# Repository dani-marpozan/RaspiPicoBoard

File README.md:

# Raspberry Pi Pico dev board 

This project is based on RP2040 microcontroller

Model 3D

## Schematic

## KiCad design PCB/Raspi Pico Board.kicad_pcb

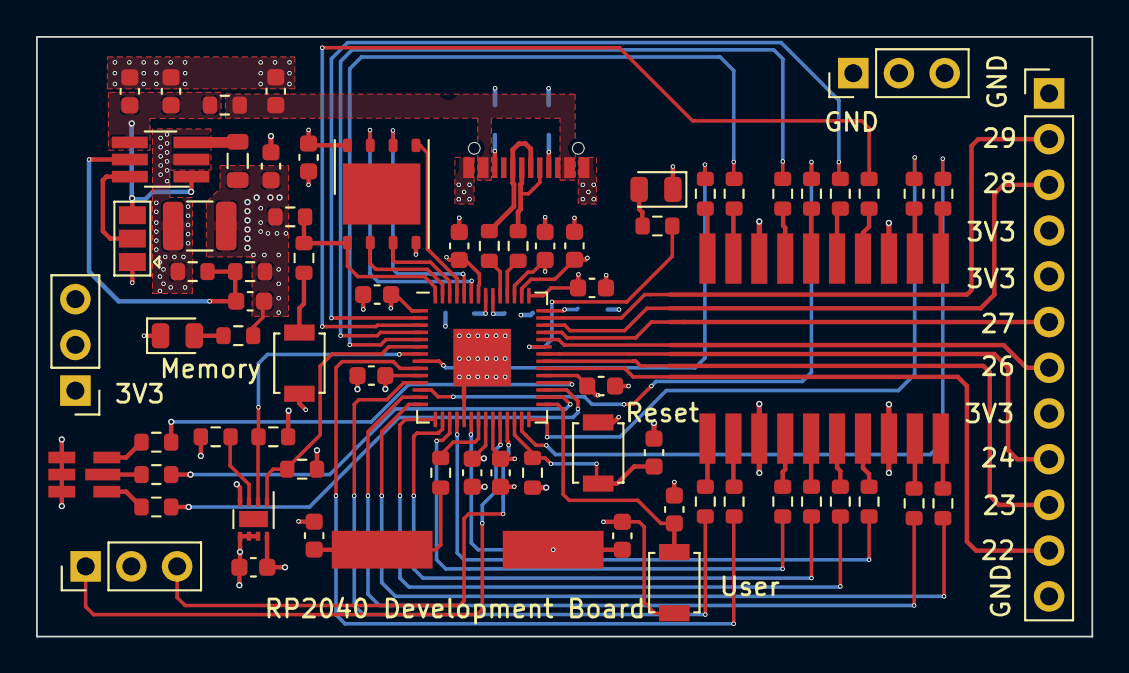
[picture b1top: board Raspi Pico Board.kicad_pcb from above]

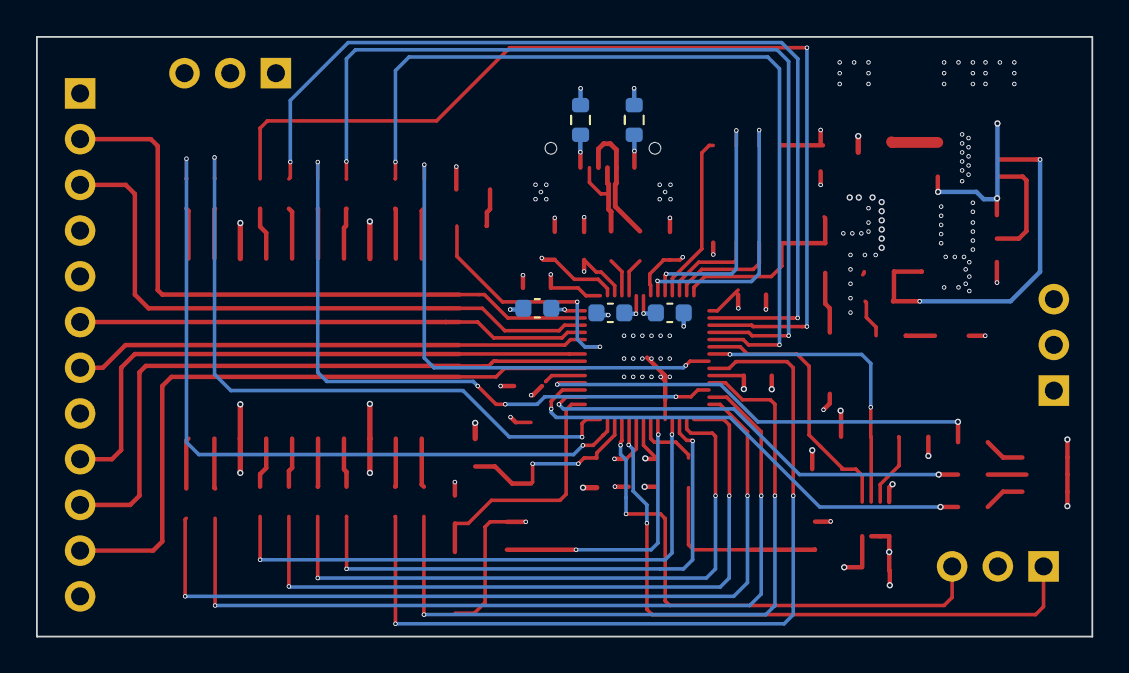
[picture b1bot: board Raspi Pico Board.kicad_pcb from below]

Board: 4 copper layers, 58.6 x 33.3 mm, 78 parts (5 on the bottom side), 79 nets.

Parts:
C1, C2, C7, C8, C9, C10, C11, C12, C15, C16, C17, C18, C19, C22, C23: 100n; C_0603_1608Metric
C3, C4: 2u2; C_0603_1608Metric
C5, C13, C14: 1u; C_0603_1608Metric
C6: 33u; C_1210_3225Metric
C20, C21: 27p; C_0603_1608Metric
C24: 10n; C_0603_1608Metric
D1, D2: LED; LED_0805_2012Metric
D4: ARGB1313HS-TR; RGB_ARGB1313HS-TR
FB1: 120R; R_0603_1608Metric
J1: USB4105; USBC_4105
J2, J4, J5: Conn_01x03_Pin; PinHeader_1x03_P2.54mm_Vertical
J3: Conn_01x12_Pin; PinHeader_1x12_P2.54mm_Vertical
JP1: SolderJumper_3_Open; SolderJumper-3_P1.3mm_Open_Pad1.0x1.5mm
L1: 10u; L_0805_2012Metric
R1, R2: 5k1; R_0603_1608Metric
R3: 887k; R_0603_1608Metric
R4: 280k; R_0603_1608Metric
R5: 150; R_0603_1608Metric
R6: 10k; R_0603_1608Metric
R7, R8, R11, R12, R13, R14, R15: 1k; R_0603_1608Metric
R9, R10: 27.4; R_0603_1608Metric
R16, R17, R18, R19, R20, R21, R22, R23, R24, R25, R26, R27, R28, R29, R30, R31, R32, R33, R34: 5k; R_0603_1608Metric
SW1, SW2, SW3: SW_Push; SW_SPST_B3U-1000P
U1: RP2040; QFN-56-1EP_7x7mm_P0.4mm_EP3.2x3.2mm
U2: W25Q128JV; WSON-8-1EP_6x5mm_P1.27mm_EP3.4x4.3mm
U3: LTC3405; TSOT-23-6_HandSoldering
U4: ACDC02-41SGWA-F01; 7DIG_ACDC02-41SGWA-F01
U5: TMP1075DSGT; WSON-8-1EP_2x2mm_P0.5mm_EP0.9x1.6mm
Y1: ABLS-12.000MHZ-B4-T

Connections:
+1V1: C14.1, C15.1, C16.1, U1.23 (DVDD), U1.45 (VREG_VOUT), U1.50 (DVDD)
+3V3: C4.1, C5.1, C6.1, C7.1, C8.1, C9.1, C10.1, C11.1, C12.1, C13.1, C17.1, C18.1, C19.1, C24.1, J3.4, J3.5, J3.8, J5.1, J5.2, J5.3, L1.2, R3.1, R5.1, R6.1, R11.2, R16.2, R17.2, R18.2, U1.1 (IOVDD), U1.10 (IOVDD), U1.22 (IOVDD), U1.33 (IOVDD), U1.42 (IOVDD), U1.43 (ADC_AVDD), U1.44 (VREG_VIN), U1.48 (USB_VDD), U1.49 (IOVDD), U2.8 (VCC), U5.8 (V+)
/Microcontroller/GPIO22: J3.11, U1.34 (GPIO22)
/Microcontroller/GPIO23: J3.10, U1.35 (GPIO23)
/Microcontroller/GPIO24: J3.9, U1.36 (GPIO24)
/Microcontroller/GPIO26: J3.7, U1.38 (GPIO26/ADC0)
/Microcontroller/GPIO27: J3.6, U1.39 (GPIO27/ADC1)
/Microcontroller/GPIO28: J3.3, U1.40 (GPIO28/ADC2)
/Microcontroller/GPIO29: J3.2, U1.41 (GPIO29/ADC3)
/Microcontroller/I2C0_SCL: R17.1, U1.7 (GPIO5), U5.2 (SCL)
/Microcontroller/I2C0_SDA: R18.1, U1.6 (GPIO4), U5.1 (SDA)
/Microcontroller/LED: R12.2, U1.37 (GPIO25)
/Microcontroller/LED_B: R13.2, U1.32 (GPIO21)
/Microcontroller/LED_G: R15.2, U1.31 (GPIO20)
/Microcontroller/LED_R: R14.2, U1.30 (GPIO19)
/Microcontroller/MCU_RUN: C22.2, R11.1, SW1.1, U1.26 (RUN)
/Microcontroller/QSPI_SCLK: U1.52 (QSPI_SCLK), U2.6 (CLK)
/Microcontroller/QSPI_SD0: U1.53 (QSPI_SD0), U2.5 (DI)
/Microcontroller/QSPI_SD1: U1.55 (QSPI_SD1), U2.2 (DO)
/Microcontroller/QSPI_SD2: U1.54 (QSPI_SD2), U2.3 (/WP)
/Microcontroller/QSPI_SD3: U1.51 (QSPI_SD3), U2.7 (/HOLD/RESET)
/Microcontroller/QSPI_SS_N: R6.2, R7.2, U1.56 (QSPI_SS_N), U2.1 (/CS)
/Microcontroller/SWCLK: J2.1, U1.24 (SWCLK)
/Microcontroller/SWDIO: J2.3, U1.25 (SWDIO)
/Microcontroller/USB_M_N: R10.2, U1.46 (USB_DM)
/Microcontroller/USB_M_P: R9.2, U1.47 (USB_DP)
/Microcontroller/USB_N: J1.A7 (DN1), J1.B7 (DN2), R10.1
/Microcontroller/USB_P: J1.A6 (DP1), J1.B6 (DP2), R9.1
/Microcontroller/USER_BUTTON: C23.2, SW3.1, U1.29 (GPIO18)
/Microcontroller/XIN: C21.1, U1.20 (XIN), Y1.2
/Microcontroller/XOUT: R8.2, U1.21 (XOUT)
/Microcontroller/display_A1: R27.2, U1.17 (GPIO14)
/Microcontroller/display_A2: R19.1, U1.13 (GPIO10)
/Microcontroller/display_B1: R28.2, U1.16 (GPIO13)
/Microcontroller/display_B2: R20.1, U1.14 (GPIO11)
/Microcontroller/display_C1: R29.2, U1.4 (GPIO2)
/Microcontroller/display_C2: R21.1, U1.28 (GPIO17)
/Microcontroller/display_D1: R30.2, U1.5 (GPIO3)
/Microcontroller/display_D2: R22.1, U1.3 (GPIO1)
/Microcontroller/display_DP1: R34.2, U1.12 (GPIO9)
/Microcontroller/display_DP2: R26.1, U1.27 (GPIO16)
/Microcontroller/display_E1: R31.2, U1.8 (GPIO6)
/Microcontroller/display_E2: R23.1, U1.2 (GPIO0)
/Microcontroller/display_F1: R32.2, U1.9 (GPIO7)
/Microcontroller/display_F2: R24.1, U1.18 (GPIO15)
/Microcontroller/display_G1: R33.2, U1.11 (GPIO8)
/Microcontroller/display_G2: R25.1, U1.15 (GPIO12)
/USBC and Power/+5V_FB: C2.1, C3.1, FB1.2, JP1.3 (B), U3.1 (RUN), U3.4 (VIN)
/USBC and Power/BCK_FB: C4.2, R3.2, R4.1, U3.5 (VFB)
/USBC and Power/BCK_MODE: JP1.2 (C), U3.6 (MODE)
/USBC and Power/LED_POW_A: D1.2 (A), R5.2
/USBC and Power/SW_NODE: L1.1, U3.3 (SW)
/USBC and Power/VBUS: C1.1, FB1.1, J1.A4 (VBUS), J1.A9 (VBUS), J1.B4 (VBUS), J1.B9 (VBUS)
GND: C1.2, C2.2, C3.2, C5.2, C6.2, C7.2, C8.2, C9.2, C10.2, C11.2, C12.2, C13.2, C14.2, C15.2, C16.2, C17.2, C18.2, C19.2, C20.2, C21.2, C22.1, C23.1, C24.2, D1.1 (K), D2.1 (K), D4.1 (RK), D4.2 (GK), D4.3 (BK), J1.A1 (GND), J1.A12 (GND), J1.B1 (GND), J1.B12 (GND), J2.2, J3.1, J3.12, J4.1, J4.2, J4.3, JP1.1 (A), R1.1, R2.1, R4.2, SW1.2, SW2.1, SW3.2, U1.19 (TESTEN), U1.57 (GND), U2.4 (GND), U3.2 (GND), U4.3 (CC), U4.8 (CC), U4.13 (CC), U4.18 (CC), U5.4 (GND), U5.5 (A2), U5.6 (A1), U5.7 (A0)
unnamed: C20.1, R8.1, Y1.1
unnamed: D2.2 (A), R12.1
unnamed: D4.4 (BA), R15.1
unnamed: D4.5 (GA), R14.1
unnamed: D4.6 (RA), R13.1
unnamed: J1.A5 (CC1), R1.2
unnamed: J1.B5 (CC2), R2.2
unnamed: R7.1, SW2.2
unnamed: R34.1, U4.5 (DP1)
unnamed: R26.2, U4.10 (DP_2)
unnamed: R27.1, U4.17 (a_1)
unnamed: R19.2, U4.12 (a_2)
unnamed: R28.1, U4.16 (b_1)
unnamed: R20.2, U4.11 (b_2)
unnamed: R29.1, U4.4 (c_1)
unnamed: R21.2, U4.9 (c_2)
unnamed: R30.1, U4.2 (d_1)
unnamed: R22.2, U4.7 (d_2)
unnamed: R31.1, U4.1 (e_1)
unnamed: R23.2, U4.6 (e_2)
unnamed: R32.1, U4.19 (f_1)
unnamed: R24.2, U4.14 (f_2)
unnamed: R33.1, U4.20 (g_1)
unnamed: R25.2, U4.15 (g_2)
unnamed: R16.1, U5.3 (ALERT)

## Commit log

2023-03-22 firs commit
2023-03-22 README.md added
2023-03-22 uc sheet modified
2023-03-31 New sheet added
2023-04-15 Layout complted, gerber files generated
2023-04-17 Layout changed, USB-C socket moved on the other side of the PCB, almost complted. DRC to be done
2023-04-19 Layout finished, gerber files generated, ready to send the design to manufacturer
